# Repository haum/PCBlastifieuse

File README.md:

# PCBlastifieuse

Une plastifieuse A3 qui peut également transférer du toner pour fabriquer des
PCBs !

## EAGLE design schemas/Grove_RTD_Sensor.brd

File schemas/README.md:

# Schéma électrique de la plastifieuse

Ce dossier contient le schéma du montage électrique d’origine de la
plastifieuse.

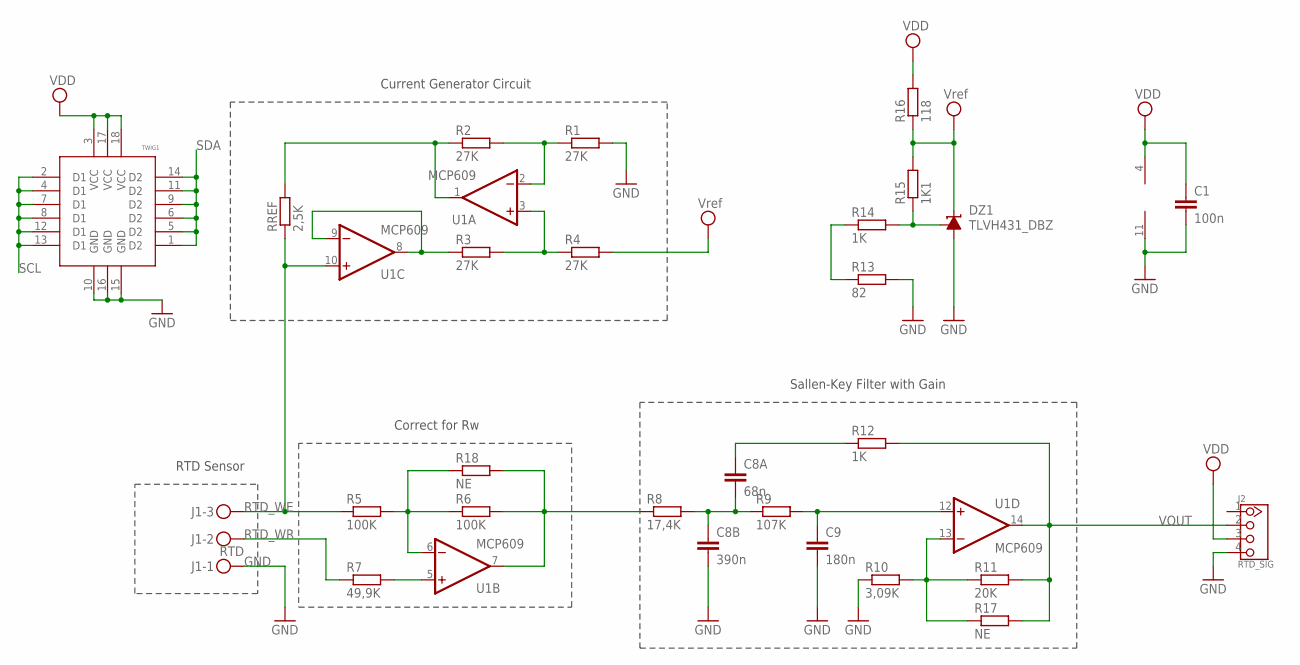
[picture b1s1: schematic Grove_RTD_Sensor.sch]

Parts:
C1: 100n; C0805
C8A: 68n; C0805
C8B: 390n; C0805
C9: 180n; C0805
DZ1: TLVH431_DBZ; SOT23
J1: RTD; MKDSN1,5/3-5,08
J2: RTD_SIG; 2.0_1X4
R1, R2, R3, R4: 27K; R0805
R5, R6: 100K; R0805
R7: 49,9K; R0805
R8: 17,4K; R0805
R9: 107K; R0805
R10: 3,09K; R0805
R11: 20K; R0805
R12, R14: 1K; R0805
R13: 82; R0805
R15: 1K1; R0805
R16: 118; R0805
R17, R18: NE; R0805
RREF: 2,5K; R0805
TWIG1: TWIG-U2'HOLES'; U2_HOLES
U1: MCP609; SO14

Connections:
GND: C1.2, C8B.2, C9.2, DZ1.3 (A), J1.1, J2.4, R1.2, R10.1, R13.2, TWIG1.10 (GND), TWIG1.15 (GND), TWIG1.16 (GND), U1.11 (V-)
unnamed: R1.1, R2.2, U1.2 (-IN)
unnamed: R3.2, R4.1, U1.3 (+IN)
unnamed: R2.1, RREF.2, U1.1 (OUT)
unnamed: R3.1, U1.8 (OUT), U1.9 (-IN)
unnamed: DZ1.1 (FB), R14.2, R15.1
unnamed: R6.2, R8.1, R18.2, U1.7 (OUT)
unnamed: R7.2, U1.5 (+IN)
unnamed: R5.2, R6.1, R18.1, U1.6 (-IN)
unnamed: R13.1, R14.1
unnamed: C9.1, R9.2, U1.12 (+IN)
unnamed: C8A.2, C8B.1, R8.2, R9.1
unnamed: R10.2, R11.1, R17.1, U1.13 (-IN)
unnamed: C8A.1, R12.1
RTD_WE: J1.3, R5.1, RREF.1, U1.10 (+IN)
RTD_WR: J1.2, R7.1
SCL: TWIG1.2 (D1), TWIG1.4 (D1), TWIG1.7 (D1), TWIG1.8 (D1), TWIG1.12 (D1), TWIG1.13 (D1)
SDA: TWIG1.1 (D2), TWIG1.5 (D2), TWIG1.6 (D2), TWIG1.9 (D2), TWIG1.11 (D2), TWIG1.14 (D2)
VDD: C1.1, J2.3, R16.2, TWIG1.3 (VCC), TWIG1.17 (VCC), TWIG1.18 (VCC), U1.4 (V+)
VEE: DZ1.2 (C), R4.2, R15.2, R16.1
VOUT: J2.2, R11.2, R12.2, R17.2, U1.14 (OUT)

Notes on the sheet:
Current Generator Circuit
RTD Sensor
Correct for Rw
Sallen-Key Filter with Gain

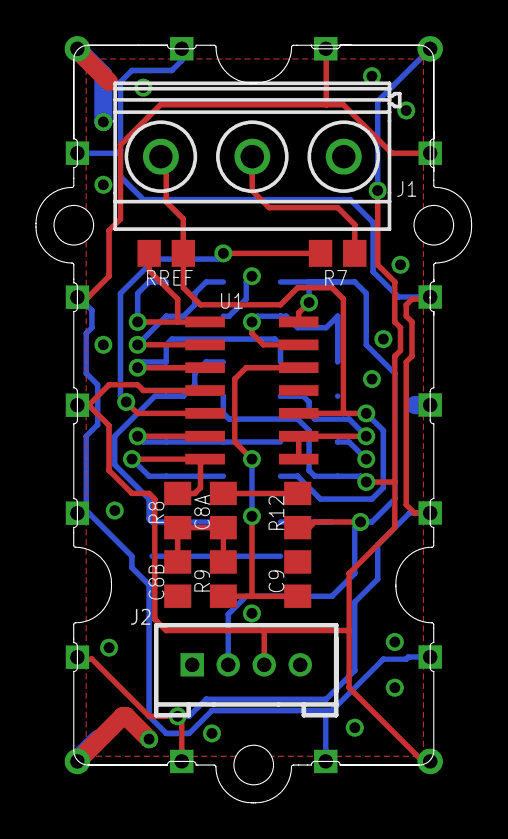
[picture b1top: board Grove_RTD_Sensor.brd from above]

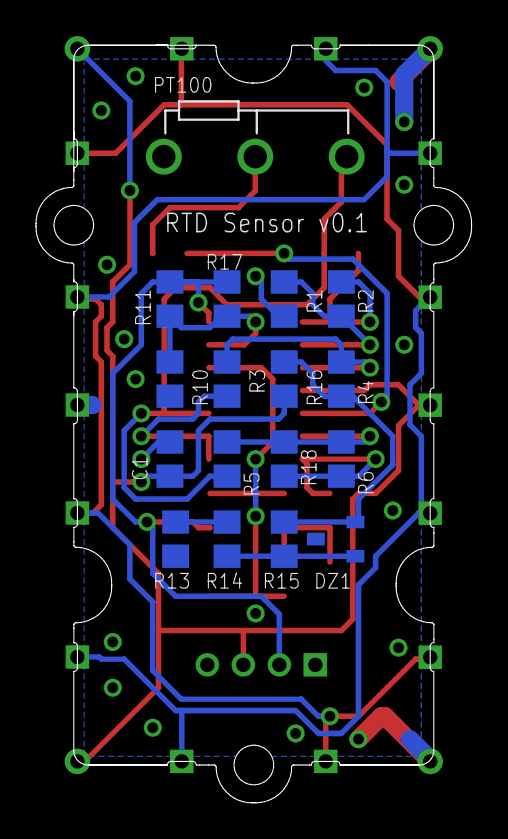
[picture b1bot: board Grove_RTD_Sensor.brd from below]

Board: 2 copper layers, 24.2 x 42.1 mm, 28 parts (16 on the bottom side), 21 nets.

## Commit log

2015-06-26 Ajout code source carte Arduino
2015-06-26 Ajout des mesures effectuées
2015-07-04 Improved README
2015-07-04 Moved schemas to their own dir
2015-07-04 Added some documentation
2015-07-04 Display schema in README
2015-07-04 Using PNG instead of SVG
    Bug in GH:
    https://github.com/isaacs/github/issues/316
2015-10-14 Cool unicode arrow in mesures/README.md
2015-10-14 Rename data.dat to data.txt
2015-11-11 Ajout données mesurées + graphique
2015-12-03 ajout documentation - schemas relay et conditioneur de capteur de temperature PCBlastivieuse V1 - Documents utilisation controleur PID PCBlastifieuse V2
